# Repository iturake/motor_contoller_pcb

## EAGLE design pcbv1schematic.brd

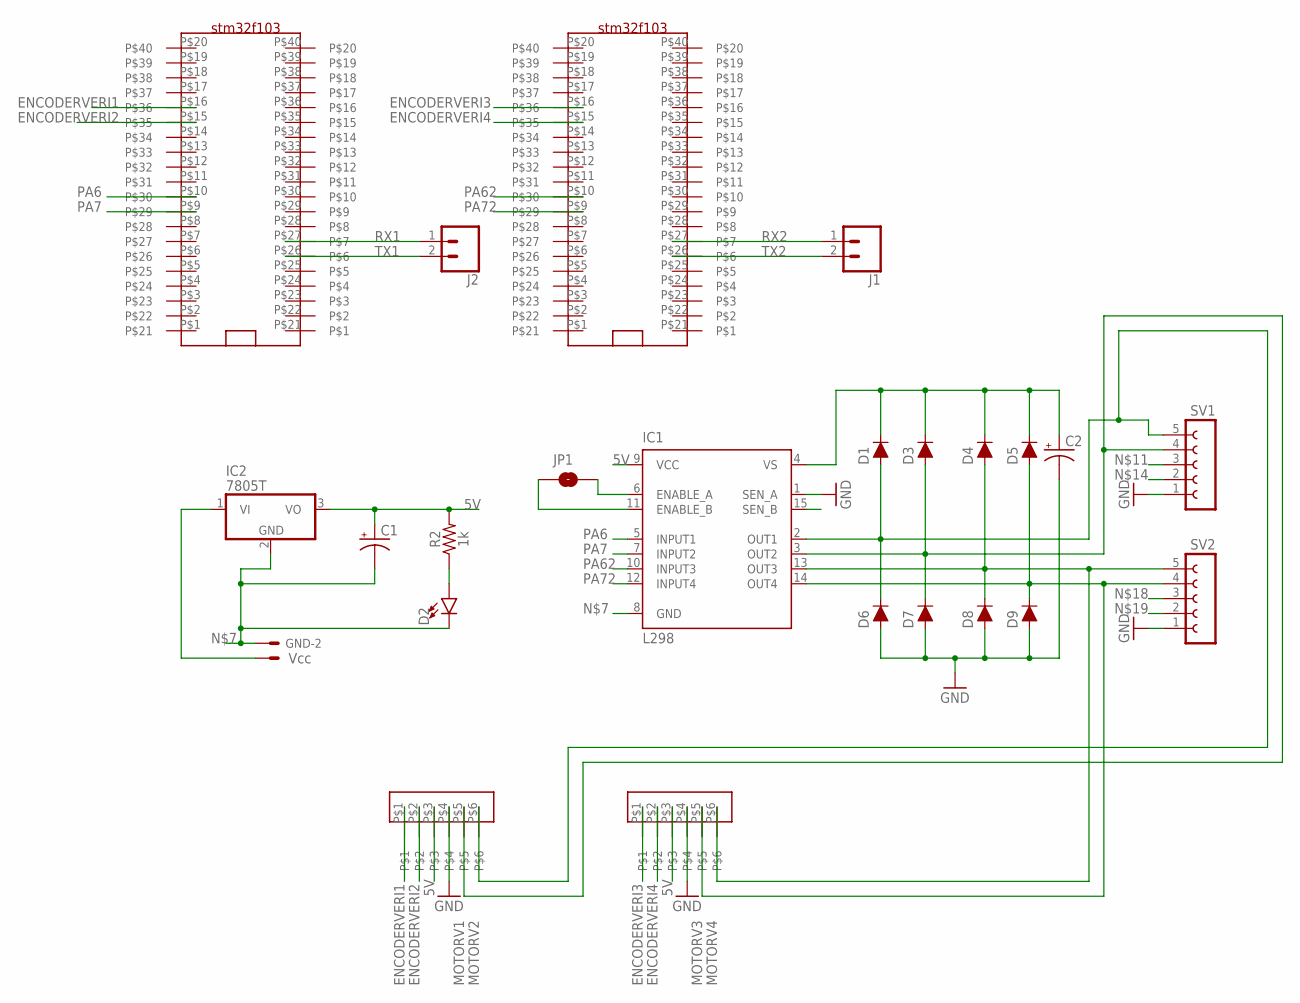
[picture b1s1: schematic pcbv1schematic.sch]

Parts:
C1, C2: 1mf; CPOL-RADIAL-5MM-10MM-KIT
D1, D3, D4, D5, D6, D7, D8, D9: 200mA/100V/1V; DIODE-1N4148
D2: LED0603; LED-0603
GND: Vcc; 22-23-2021
IC1: L298; MULTIWATT-15
IC2: 7805T; TO220H
J1, J2: CONN_02; 1X02
JP1: JUMPER-SMT_2_NO_NO-SILK; SMT-JUMPER_2_NO_NO-SILK
R2: 1k; 0603
SV1, SV2: FE05-1
U$1, U$2: STM32F103
U$3, U$4: KLAMENS6

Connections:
5V: C1.+, IC1.9 (VCC), IC2.3 (VO), R2.2, U$3.P$3, U$4.P$3
ENCODERVERI1: U$2.P$16, U$3.P$1
ENCODERVERI2: U$2.P$15, U$3.P$2
ENCODERVERI3: U$1.P$16, U$4.P$1
ENCODERVERI4: U$1.P$15, U$4.P$2
MOTORV1: D3.A, D7.C, IC1.3 (OUT2), SV1.4, U$3.P$5
MOTORV2: D1.A, D6.C, IC1.2 (OUT1), SV1.5, U$3.P$6
MOTORV3: D5.A, D9.C, IC1.14 (OUT4), SV2.4, U$4.P$5
MOTORV4: D4.A, D8.C, IC1.13 (OUT3), SV2.5, U$4.P$6
unnamed: GND.2, IC2.1 (VI)
unnamed: IC1.11 (ENABLE_B), JP1.1
unnamed: D2.A, R2.1
unnamed: C1.-, C2.-, D2.C, D6.A, D7.A, D8.A, D9.A, GND.1, IC1.1 (SEN_A), IC1.8 (GND), IC2.2 (GND), SV1.1, SV2.1, U$3.P$4, U$4.P$4
unnamed: IC1.6 (ENABLE_A), JP1.2
OUT1: C2.+, D1.C, D3.C, D4.C, D5.C, IC1.4 (VS)
PA6: IC1.5 (INPUT1), U$2.P$10
PA7: IC1.7 (INPUT2), U$2.P$9
PA62: IC1.10 (INPUT3), U$1.P$10
PA72: IC1.12 (INPUT4), U$1.P$9
RX1: J2.1, U$2.P$27
RX2: J1.1, U$1.P$27
TX1: J2.2, U$2.P$26
TX2: J1.2, U$1.P$26

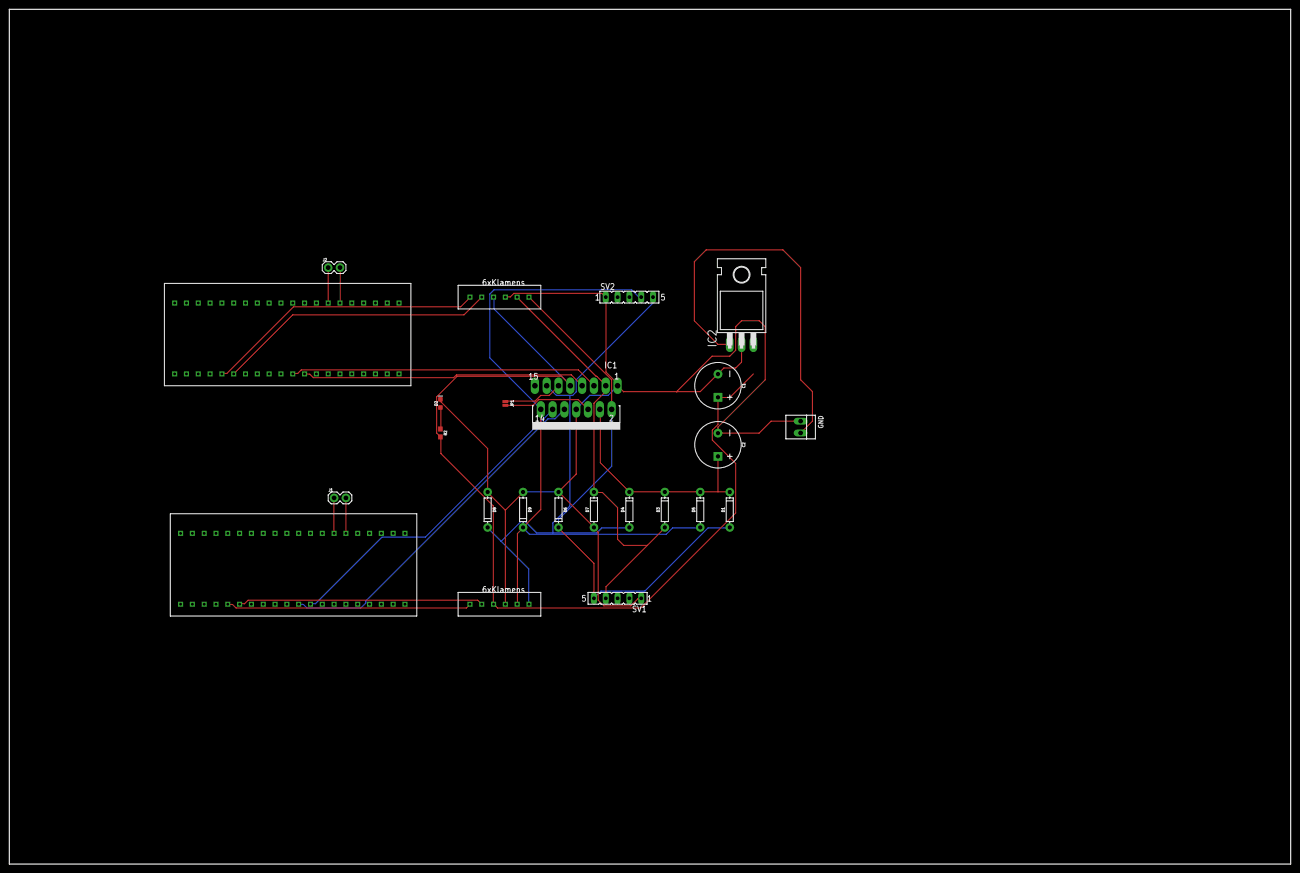
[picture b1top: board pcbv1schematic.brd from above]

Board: 2 copper layers, 275.6 x 183.8 mm, 24 parts (0 on the bottom side), 23 nets.

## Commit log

2021-02-14 Fixes Label Name

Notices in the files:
parts and their libraries:
SparkFun-Capacitors: Licensing: Creative Commons ShareAlike 4.0 International - https://creativecommons.org/licenses/by-sa/4.0
